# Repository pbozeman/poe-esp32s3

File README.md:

# POE ESP32S3

POE enabled ESP32S3 dev board with onboard programming via USB-C,
and an OTG USB-A port. The repo contains the Kicad schematic and PCB
design.

It is ok to apply power via USB-C and POE simultaneously. The board
gives preference to the POE, if it is present.

While this can be used as a general purpose POE dev board, I personally
use it to network enable a Aeotec Zwave stick using the ser2net protocol.

## "Inspiration"

I copied the POE schematic and layout directly from [OLIMEX](https://github.com/OLIMEX/ESP32-POE-ISO/blob/master/HARDWARE/ESP32-PoE-ISO-Rev.K/ESP32-PoE-ISO_Rev_K.pdf).

The Wiznet 5500 ethernet to SPI circuit was copied directly from the
[WS5500 reference circuit](https://docs.wiznet.io/img/products/w5500/W5500_ds_v110e.pdf)

Everything else is from the [ES32-S3 reference circuit](https://dl.espressif.com/dl/schematics/SCH_ESP32-S3-DEVKITM-1_V1_20210310A.pdf).

## General Caveats

This was my very first PCB and there is a lot I don't like about both
the schematic and the PCB layout. I'm only making this repo public
because someone on Reddit asked for the Kicad files.

More importantly, the Olimex POE design is very noisy. It's fine for
my use, but I heard from someone else that used an Olimex like design
that it was too noisy to use directly with an ADC.

If I were to do this again, I would base the POE design around Silvertel
POE modules, potentially using them directly. I measured one and it's
power was far less noisy. The entire unit is cheaper than trying to
source individual parts, and they come in form factors that should be easy
to integrate.

## Production and Update Caveats

I don't think part numbers were populated, and this may nor may not
seamlessly export with the JLCPCB exporter. The library management
is likely bad, and there is a possibility that I edited symbols or
footprints directly, without doing so in the library. There might
be non-relative paths in the library configs as well. I hadn't yet
established best practices for any of that back when I did this. So,
updating symbols and footprints might mess up the schematic and PCB.

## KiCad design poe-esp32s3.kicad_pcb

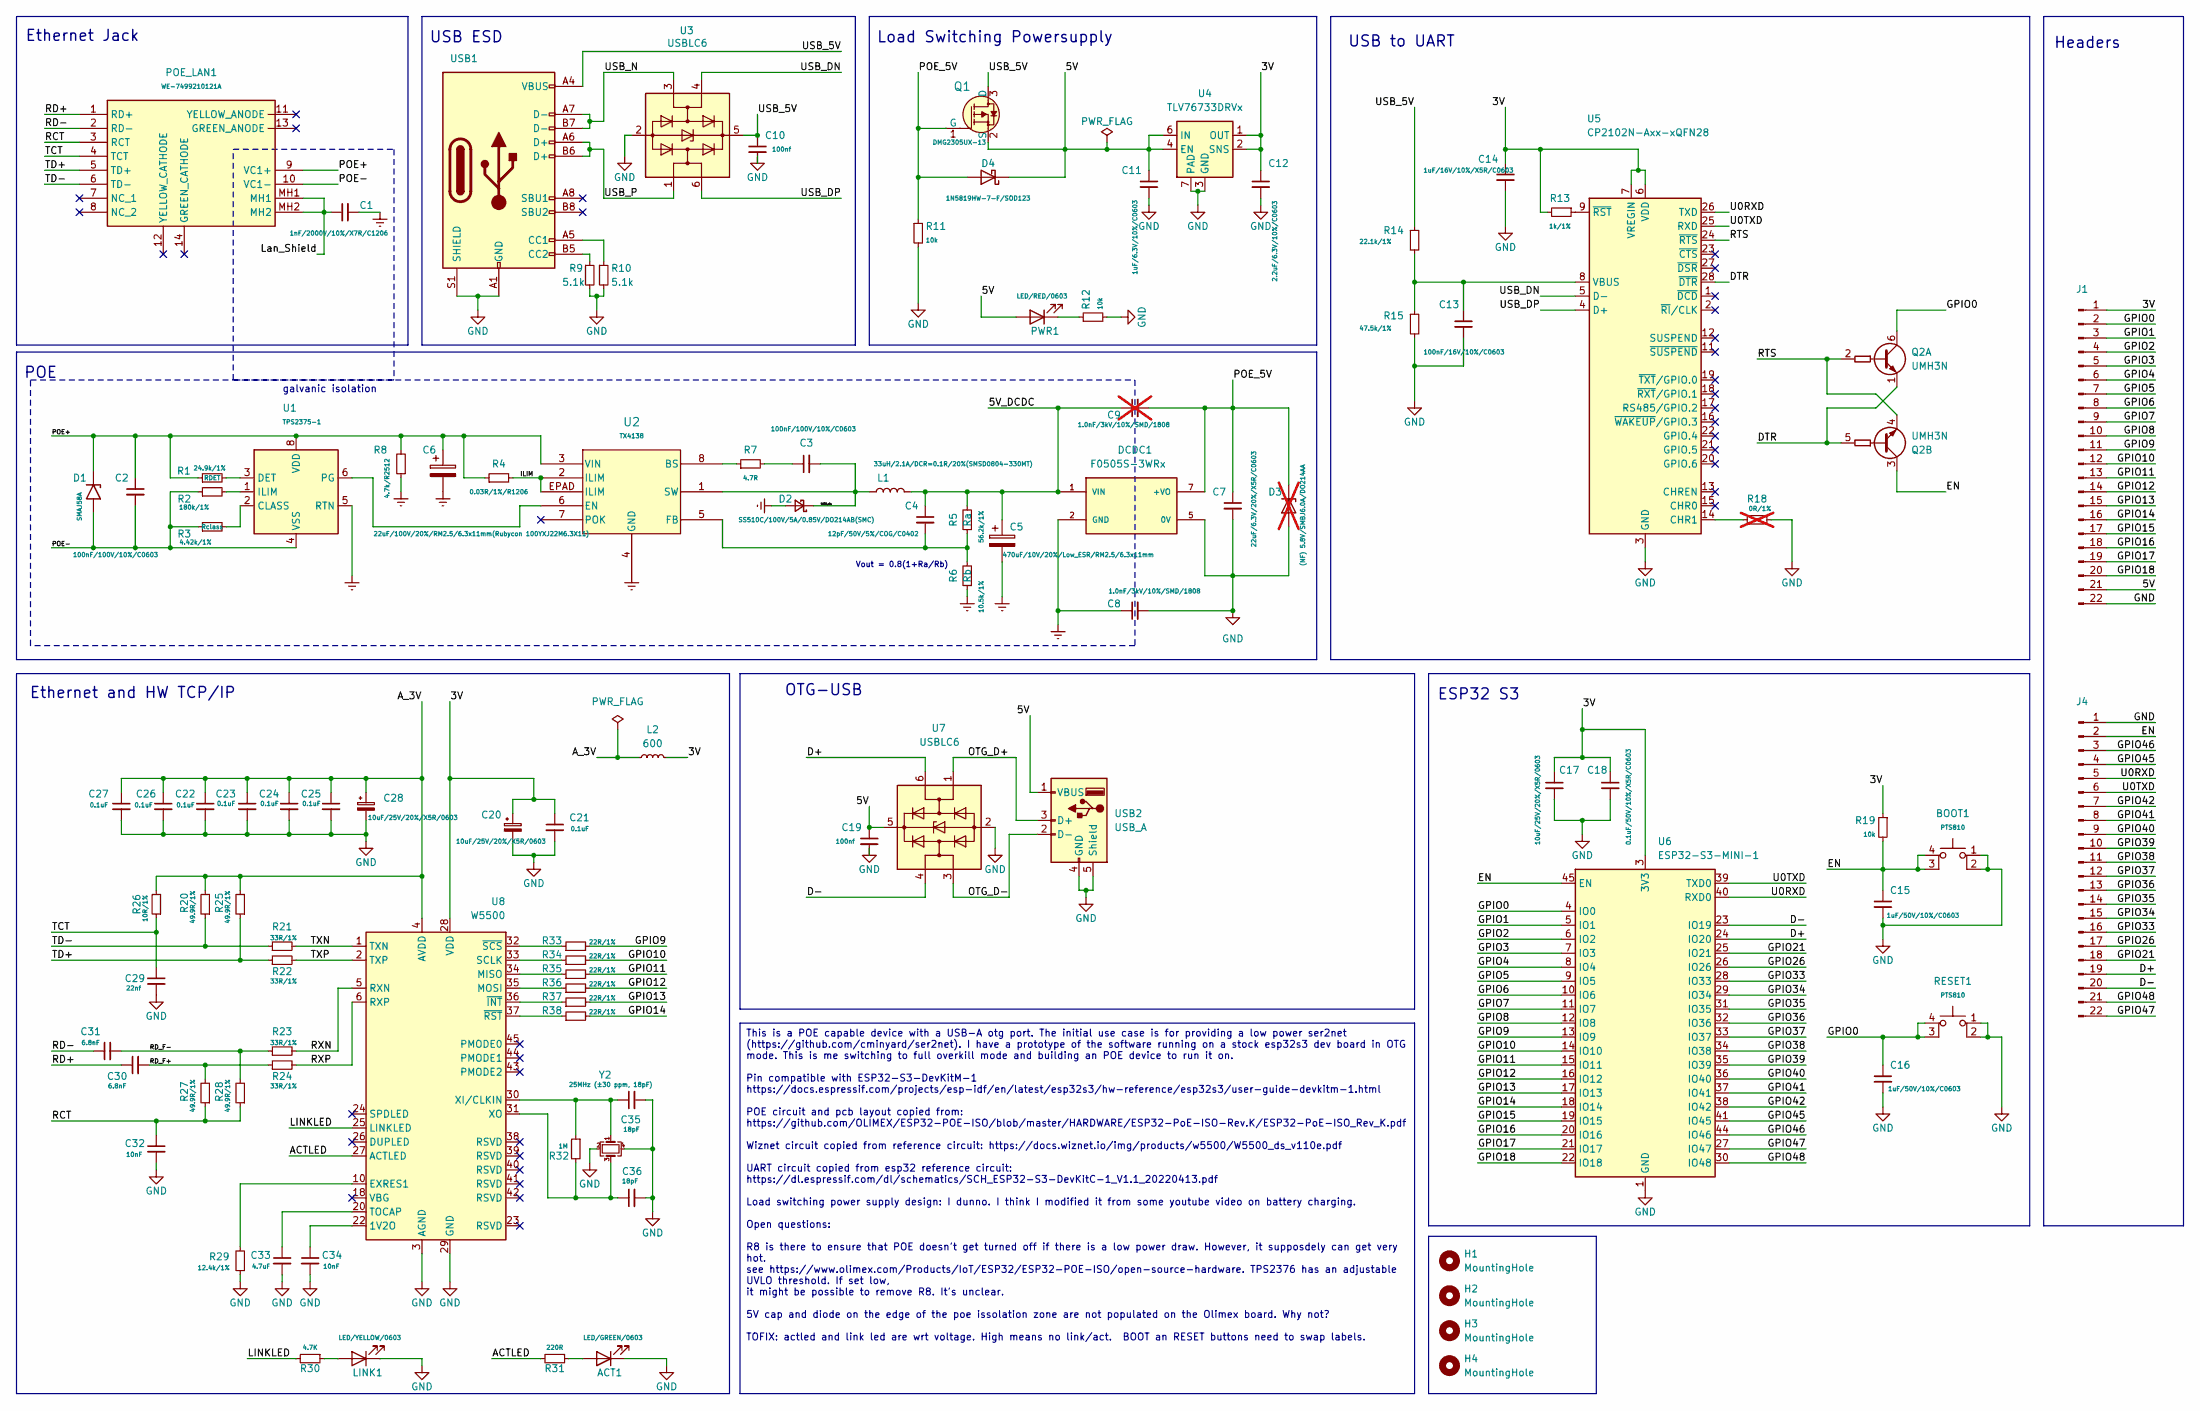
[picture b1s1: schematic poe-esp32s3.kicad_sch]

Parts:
ACT1: LED/GREEN/0603; LED_0603_1608Metric; MPN 19-21SYGC/S530-E2/TR8
BOOT1: PTS810; SW_SPST_PTS810; MPN PTS810SJG250SMTRLFS
C1: 1nF/2000V/10%/X7R/C1206; C_1206_3216Metric; MPN CC1206MKX7RDBB102
C2, C3: 100nF/100V/10%/C0603; C_0603_1608Metric; MPN CL10B104KC8NNNC
C4: 12pF/50V/5%/COG/C0402; C_0402_1005Metric; MPN 0402CG120J500NT
C5: 470uF/10V/20%/Low_ESR/RM2.5/6.3x11mm; C_Radial_D6.3mm_H11.0mm_P2.50mm; MPN 10YXJ470MFFC(6.3X11)
C6: 22uF/100V/20%/RM2.5/6.3x11mm(Rubycon 100YXJ22M6.3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; C_Radial_D6.3mm_H11.0mm_P2.50mm; MPN 100YXJ22M6.3X11
C7: 22uF/6.3V/20%/X5R/C0603; C_0603_1608Metric; MPN CL10A226MQ8NRNC
C8: 1.0nF/3kV/10%/SMD/1808; C_1808; MPN C1808N102J302T
C9: 1.0nF/3kV/10%/SMD/1808; C_1808; not fitted
C10, C19: 100nf; C_0603_1608Metric; MPN CC0603KRX7R9BB104
C11: 1uF/6.3V/10%/C0603; C_0603_1608Metric; MPN CC0603KRX5R5BB105
C12: 2.2uF/6.3V/10%/C0603; C_0603_1608Metric; MPN 06036D225KAT2A
C13: 100nF/16V/10%/C0603; C_0603_1608Metric; MPN CL10B104KO8NNNC
C14: 1uF/16V/10%/X5R/C0603; C_0603_1608Metric; MPN CL10A105KO8NNNC
C15, C16: 1uF/50V/10%/C0603; C_0603_1608Metric; MPN CL10A105KB8NNNC
C17, C20, C28: 10uF/25V/20%/X5R/0603; C_0603_1608Metric; MPN CL10A106MA8NRNC
C18: 0.1uF/50V/10%/X5R/C0603; C_0603_1608Metric; MPN CC0603KRX7R9BB104
C21, C22, C23, C24, C25, C26, C27: 0.1uF; C_0402_1005Metric; MPN CL05B104KO5NNNC
C29: 22nf; C_0402_1005Metric; MPN 0402B223K500NT
C30, C31: 6.8nF; C_0402_1005Metric; MPN 0402B682K500NT
C32, C34: 10nF; C_0402_1005Metric; MPN 0402B102K500NT
C33: 4.7uF; C_0603_1608Metric; MPN CL10A475KO8NNNC
C35, C36: 18pF; C_0402_1005Metric; MPN 0402CG180J500NT
D1: SMAJ58A; D_SMA; MPN SMAJ58A-E3/5A
D2: SS510C/100V/5A/0.85V/DO214AB(SMC); DO-214AB; MPN SS510C
D3: (NF) 5.8V/SMBJ6.0A/DO214AA; D_SMB; MPN NA; not fitted
D4: 1N5819HW-7-F/SOD123; D_SOD-123; MPN 1N5819HW-7-F
DCDC1: F0505S-3WRx; CONV_F0505S-1WR3; PARTREV 2021.12.28-A/6
H1, H2, H3, H4: MountingHole; MountingHole_2.2mm_M2; MPN NA
J1, J4: PinHeader_1x22_P2.54mm_Vertical; MPN NA
L1: 33uH/2.1A/DCR=0.1R/20%(SMSD0804-330MT); IND_IDC-5020_VIS; MPN SMSD0804-330MT
L2: 600; C_0603_1608Metric; MPN MLB1608F-121T
LINK1: LED/YELLOW/0603; LED_0603_1608Metric; MPN 19-213/Y2C-CQ2R2L/3T(CY)
POE_LAN1: WE-7499210121A; 7499210121A; Manufacturer_Part_Number 7499210121A; Mouser Part Number 710-7499210121A
PWR1: LED/RED/0603; LED_0603_1608Metric; MPN KT-0603R
Q1: DMG2305UX-13; SOT-23-3; MPN DMG2305UX-13; Digi-Key_PN DMG2305UX-13DICT-ND
Q2: UMH3N; SOT-363_SC-70-6; MPN UMH3N
R1: 24.9k/1%; R_0402_1005Metric; MPN 0402WGF2492TCE
R2: 180k/1%; R_0402_1005Metric; MPN CR0402FF1803G
R3: 4.42k/1%; R_0402_1005Metric; MPN CR0402FF4421G
R4: 0.03R/1%/R1206; R_1206_3216Metric; MPN 1206W3F300MT5E
R5: 56.2k/1%; R_0402_1005Metric; MPN RC-02W5622FT
R6: 10.5k/1%; R_0402_1005Metric; MPN RC0402FR-0710K5L
R7: 4.7R; R_0402_1005Metric; MPN 0402WGF470KTCE
R8: 4.7k/R2512; R_2512_6332Metric; MPN RMC25124.7K1%N
R9, R10: 5.1k; R_0402_1005Metric; MPN 0402WGF5101TCE
R11, R12, R19: 10k; R_0402_1005Metric; MPN 0402WGF1002TCE
R13: 1k/1%; R_0402_1005Metric; MPN 0402WGF1001TCE
R14: 22.1k/1%; R_0402_1005Metric; MPN RC0402FR-0722K1L
R15: 47.5k/1%; R_0402_1005Metric; MPN 0402WGF4752TCE
R18: 0R/1%; R_0603_1608Metric; MPN 0603WAF0000T5E; not fitted
R20, R25, R27, R28: 49.9R/1%; R_0402_1005Metric; MPN 0402WGF499JTCE
R21, R22, R23, R24: 33R/1%; R_0402_1005Metric; MPN 0402WGF330JTCE
R26: 10R/1%; R_0402_1005Metric; MPN 0402WGF100JTCE
R29: 12.4k/1%; R_0402_1005Metric; MPN RC0402FR-0712K4L
R30: 4.7K; R_0402_1005Metric; MPN 0402WGF4701TCE
R31: 220R; R_0402_1005Metric; MPN 0402WGF2200TCE
R32: 1M; R_0402_1005Metric; MPN CRG0402F1M0
R33, R34, R35, R36, R37, R38: 22R/1%; R_0402_1005Metric; MPN 0402WGF220JTCE
RESET1: PTS810; SW_SPST_PTS810; MPN PTS810SJG250SMTRLFS
U1: TPS2375-1; TSSOP-8_4.4x3mm_P0.65mm; MPN TPS2375PW-1
U2: TX4138; tx4138-ESOIC8_XDS; MPN TX4138
U3, U7: USBLC6; SOT-666; MPN USBLC6-2P6
U4: TLV76733DRVx; WSON-6-1EP_2x2mm_P0.65mm_EP1x1.6mm_ThermalVias; MPN TLV76733DRVR
U5: CP2102N-Axx-xQFN28; QFN-28-1EP_5x5mm_P0.5mm_EP3.35x3.35mm; MPN CP2102N-A02-GQFN28R
U6: ESP32-S3-MINI-1; ESP32-S2-MINI-1; MPN ESP32-S3-MINI-1-N8
U8: W5500; LQFP-48_7x7mm_P0.5mm; MPN W5500
USB1: USB_C_Receptacle_USB2.0_16P; USB_C_Receptacle_GCT_USB4105-xx-A_16P_TopMnt_Horizontal; MPN GT-USB-7004
USB2: USB_A; usb-a-U-A-24DD-W-9; MPN U-A-24DD-W-9
Y2: 25MHz (±30 ppm, 18pF); Crystal_SMD_3225-4Pin_3.2x2.5mm; MPN S322525M18PF10PPM

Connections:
/3V: C12.1, C14.1, C17.1, C18.1, C20.1, C21.1, J1.1, L2.2, R13.2, R19.1, U4.1 (OUT), U4.2 (SNS), U5.6 (VDD), U5.7 (VREGIN), U6.3 (3V3), U8.28 (VDD)
/5V: C11.1, C19.1, D4.1 (K), J1.21, PWR1.2 (A), Q1.2 (S), U4.4 (EN), U4.6 (IN), U7.5 (VBUS), USB2.1 (VBUS)
/5V_DCDC: C4.1, C5.1, C9.1, DCDC1.1 (VIN), L1.2, R5.2
/4138_da: C3.2, D2.1 (K), L1.1, U2.1 (SW)
/ACTLED: R31.2, U8.27 (ACTLED)
/A_3V: C22.1, C23.1, C24.1, C25.1, C26.1, C27.1, C28.1, L2.1, R20.2, R25.2, R26.2, U8.4 (AVDD), U8.8 (AVDD), U8.11 (AVDD), U8.15 (AVDD), U8.17 (AVDD), U8.21 (AVDD)
/D+: J4.19, U6.24 (IO20), U7.6 (I/O1)
/D-: J4.20, U6.23 (IO19), U7.4 (I/O2)
/DTR: Q2.1 (E1), Q2.5 (B2), U5.28 (~DTR)
/EN: BOOT1.3 (K), BOOT1.4 (A), C15.1, J4.2, Q2.3 (C2), R19.2, U6.45 (EN)
/GPIO0: C16.1, J1.2, Q2.6 (C1), RESET1.3 (K), RESET1.4 (A), U6.4 (IO0)
/GPIO1: J1.3, U6.5 (IO1)
/GPIO2: J1.4, U6.6 (IO2)
/GPIO3: J1.5, U6.7 (IO3)
/GPIO4: J1.6, U6.8 (IO4)
/GPIO5: J1.7, U6.9 (IO5)
/GPIO6: J1.8, U6.10 (IO6)
/GPIO7: J1.9, U6.11 (IO7)
/GPIO8: J1.10, U6.12 (IO8)
/GPIO9: J1.11, R33.2, U6.13 (IO9)
/GPIO10: J1.12, R34.2, U6.14 (IO10)
/GPIO11: J1.13, R35.2, U6.15 (IO11)
/GPIO12: J1.14, R36.2, U6.16 (IO12)
/GPIO13: J1.15, R37.2, U6.17 (IO13)
/GPIO14: J1.16, R38.2, U6.18 (IO14)
/GPIO15: J1.17, U6.19 (IO15)
/GPIO16: J1.18, U6.20 (IO16)
/GPIO17: J1.19, U6.21 (IO17)
/GPIO18: J1.20, U6.22 (IO18)
/GPIO21: J4.18, U6.25 (IO21)
/GPIO26: J4.17, U6.26 (IO26)
/GPIO33: J4.16, U6.28 (IO33)
/GPIO34: J4.15, U6.29 (IO34)
/GPIO35: J4.14, U6.31 (IO35)
/GPIO36: J4.13, U6.32 (IO36)
/GPIO37: J4.12, U6.33 (IO37)
/GPIO38: J4.11, U6.34 (IO38)
/GPIO39: J4.10, U6.35 (IO39)
/GPIO40: J4.9, U6.36 (IO40)
/GPIO41: J4.8, U6.37 (IO41)
/GPIO42: J4.7, U6.38 (IO42)
/GPIO45: J4.4, U6.41 (IO45)
/GPIO46: J4.3, U6.44 (IO46)
/GPIO47: J4.22, U6.27 (IO47)
/GPIO48: J4.21, U6.30 (IO48)
/ILIM: R4.2, U2.2 (ILIM), U2.EPAD (ILIM)
/LINKLED: R30.2, U8.25 (LINKLED)
/Lan_Shield: C1.1, POE_LAN1.MH1, POE_LAN1.MH2
/OTG_D+: U7.1 (I/O1), USB2.3 (D+)
/OTG_D-: U7.3 (I/O2), USB2.2 (D-)
/POE+: C2.1, C6.1, D1.1 (A1), POE_LAN1.9 (VC1+), R1.1, R4.1, R8.2, U1.8 (VDD), U2.3 (VIN)
/POE-: C2.2, D1.2 (A2), POE_LAN1.10 (VC1-), R2.1, R3.1, U1.4 (VSS)
/POE_5V: C7.1, C9.2, D3.1 (K), D4.2 (A), DCDC1.7 (+VO), Q1.1 (G), R11.1
/RCT: C32.1, POE_LAN1.3 (RCT), R27.1, R28.1
/RD+: C30.1, POE_LAN1.1 (RD+)
/RD-: C31.1, POE_LAN1.2 (RD-)
/RD_F+: C30.2, R24.1, R27.2
/RD_F-: C31.2, R23.1, R28.2
/RTS: Q2.2 (B1), Q2.4 (E2), U5.24 (~RTS)
/RXN: R23.2, U8.5 (RXN)
/RXP: R24.2, U8.6 (RXP)
/TCT: C29.1, POE_LAN1.4 (TCT), R26.1
/TD+: POE_LAN1.5 (TD+), R22.1, R25.1
/TD-: POE_LAN1.6 (TD-), R20.1, R21.1
/TXN: R21.2, U8.1 (TXN)
/TXP: R22.2, U8.2 (TXP)
/U0RXD: J4.5, U5.26 (TXD), U6.40 (RXD0)
/U0TXD: J4.6, U5.25 (RXD), U6.39 (TXD0)
/USB_5V: C10.1, Q1.3 (D), R14.1, U3.5 (VBUS), USB1.A4 (VBUS), USB1.A9 (VBUS), USB1.B4 (VBUS), USB1.B9 (VBUS)
/USB_DN: U3.4 (I/O2), U5.5 (D-)
/USB_DP: U3.6 (I/O1), U5.4 (D+)
/USB_N: U3.3 (I/O2), USB1.A7 (D-), USB1.B7 (D-)
/USB_P: U3.1 (I/O1), USB1.A6 (D+), USB1.B6 (D+)
Earth: C1.2, C5.2, C6.2, C8.1, D2.2 (A), DCDC1.2 (GND), R6.1, R8.1, U1.5 (RTN), U2.4 (GND)
GND: ACT1.1 (K), BOOT1.1, BOOT1.2, C7.2, C8.2, C10.2, C11.2, C12.2, C13.2, C14.2, C15.2, C16.2, C17.2, C18.2, C19.2, C20.2, C21.2, C22.2, C23.2, C24.2, C25.2, C26.2, C27.2, C28.2, C29.2, C32.2, C33.2, C34.2, C35.2, C36.2, D3.2 (A), DCDC1.5 (0V), J1.22, J4.1, LINK1.1 (K), R9.2, R10.2, R11.2, R12.2, R15.2, R18.2, R29.1, RESET1.1, RESET1.2, U3.2 (GND), U4.3 (GND), U4.5 (GND), U4.7 (PAD), U5.3 (GND), U5.29 (GND), U6.1 (GND), U6.2 (GND), U6.42 (GND), U6.43 (GND), U6.46 (GND), U6.47 (GND), U6.48 (GND), U6.49 (GND), U6.50 (GND), U6.51 (GND), U6.52 (GND), U6.53 (GND), U6.54 (GND), U6.55 (GND), U6.56 (GND), U6.57 (GND), U6.58 (GND), U6.59 (GND), U6.60 (GND), U6.61 (GND), U6.62 (GND), U6.63 (GND), U6.64 (GND), U6.65 (GND), U7.2 (GND), U8.3 (AGND), U8.9 (AGND), U8.14 (AGND), U8.16 (AGND), U8.19 (AGND), U8.29 (GND), U8.48 (AGND), USB1.A1 (GND), USB1.A12 (GND), USB1.B1 (GND), USB1.B12 (GND), USB1.S1 (SHIELD), USB2.4 (GND), USB2.5 (Shield), Y2.2, Y2.4
unnamed: ACT1.2 (A), R31.1
unnamed: C3.1, R7.2
unnamed: LINK1.2 (A), R30.1
unnamed: PWR1.1 (K), R12.1
unnamed: R3.2, U1.2 (CLASS)
unnamed: R1.2, U1.3 (DET)
unnamed: R2.2, U1.1 (ILIM)
unnamed: U1.6 (PG), U2.6 (EN)
unnamed: R7.1, U2.8 (BS)
unnamed: C4.2, R5.1, R6.2, U2.5 (FB)
unnamed: R18.1, U5.14 (CHR1)
unnamed: C13.1, R14.2, R15.1, U5.8 (VBUS)
unnamed: R13.1, U5.9 (~RST)
unnamed: C34.1, U8.22 (1V2O)
unnamed: R29.2, U8.10 (EXRES1)
unnamed: R35.1, U8.34 (MISO)
unnamed: R36.1, U8.35 (MOSI)
unnamed: R34.1, U8.33 (SCLK)
unnamed: C33.1, U8.20 (TOCAP)
unnamed: C35.1, R32.1, U8.30 (XI/CLKIN), Y2.1
unnamed: C36.1, R32.2, U8.31 (XO), Y2.3
unnamed: R37.1, U8.36 (~INT)
unnamed: R38.1, U8.37 (~RST)
unnamed: R33.1, U8.32 (~SCS)
unnamed: R10.1, USB1.A5 (CC1)
unnamed: R9.1, USB1.B5 (CC2)

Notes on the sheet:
This is a POE capable device with a USB-A otg port. The initial use case is for providing a low power ser2net (https://github.com/cminyard/ser2net). I have a prototype of the software running on a stock esp32s3 dev board in OTG mode. This is me switching to full overkill mode and building an POE de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
Load Switching Powersupply
Vout = 0.8(1+Ra/Rb)
galvanic isolation
USB to UART
OTG-USB
POE
Ethernet and HW TCP/IP
ESP32 S3
USB ESD
Ethernet Jack
Headers

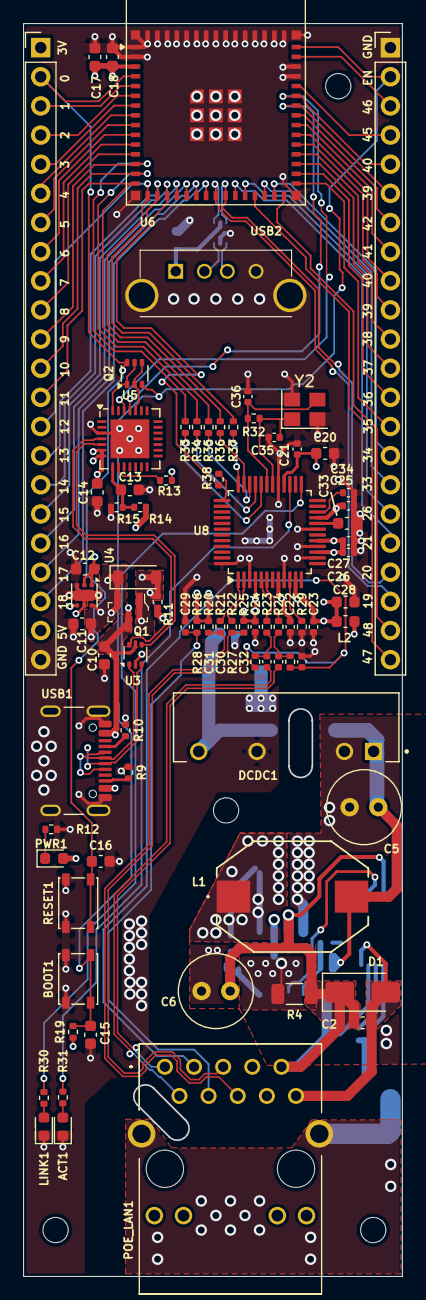
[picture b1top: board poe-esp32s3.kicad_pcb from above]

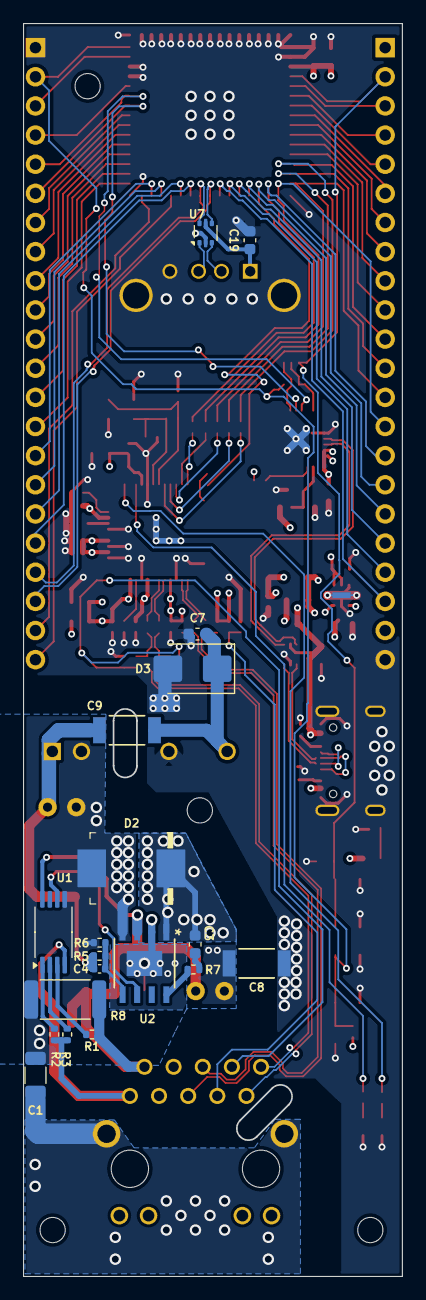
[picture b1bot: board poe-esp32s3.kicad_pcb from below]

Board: 4 copper layers, 33.0 x 109.2 mm, 103 parts (19 on the bottom side), 100 nets.

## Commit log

2024-11-25 Add readme and license
